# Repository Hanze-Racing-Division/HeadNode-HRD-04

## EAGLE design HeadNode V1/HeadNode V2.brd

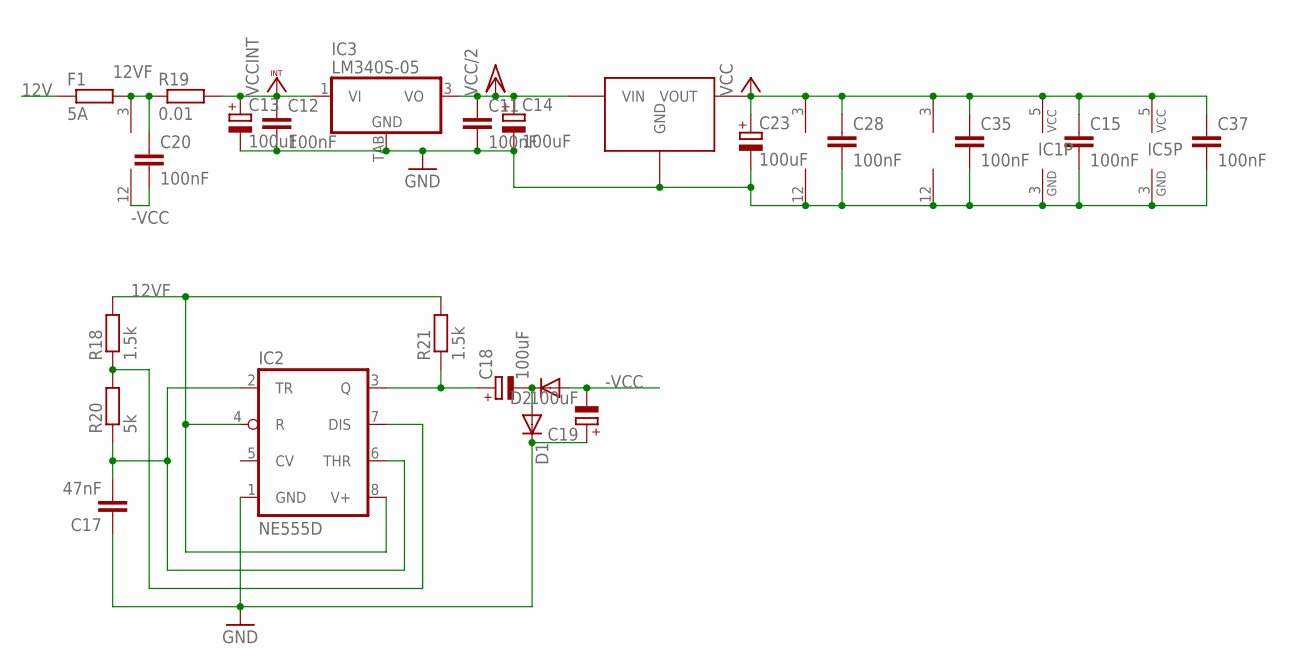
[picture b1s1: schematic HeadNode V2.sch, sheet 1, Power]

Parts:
C11, C12, C15, C20, C28, C35, C37: 100nF; C0805
C13, C14, C23: 100uF; 153CLV-0605; FARNELL 1244406RL
C17: 47nF; C0805; FARNELL MCSH31B473K160CT
C18, C19: 100uF; PANASONIC_D; FARNELL 1244406RL
D1, D2: DIODE-DO214AA; DO214AA; FARNELL SS13B
F1: 5A; R1206; FARNELL MC12CF 005
IC1, IC5: 74AHCT1G14DBV; SOT23-5
IC2: NE555D; SO08
IC3: LM340S-05; TO263-3; FARNELL LM1084ISX-5.0/NOPB
IC4, IC6, IC7: LM339D; SO14
R18, R21: 1.5k; R0805
R19: 0.01; R4527; FARNELL OARS1 - R010FI
R20: 5k; R0805
U$5: TS2940; TO-252

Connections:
12V: F1.1; also elsewhere on the board
12VF: C20.1, F1.2, IC2.4 (R), IC2.8 (V+), IC4.3 (V+), R18.2, R19.1, R21.2; also elsewhere on the board
-VCC: C19.-, C20.2, D2.A, IC4.12 (GND)
GND: C11.2, C12.2, C13.-, C14.-, C15.2, C17.1, C19.+, C23.-, C28.2, C35.2, C37.2, D1.C, IC1.3 (GND), IC2.1 (GND), IC3.TAB (GND), IC5.3 (GND), IC6.12 (GND), IC7.12 (GND), U$5.GND; also elsewhere on the board
unnamed: C18.+, IC2.3 (Q), R21.1
unnamed: C18.-, D1.A, D2.C
unnamed: IC2.7 (DIS), R18.1, R20.2
unnamed: C17.2, IC2.2 (TR), IC2.6 (THR), R20.1
VCC: C15.1, C23.+, C28.1, C35.1, C37.1, IC1.5 (VCC), IC5.5 (VCC), IC6.3 (V+), IC7.3 (V+), U$5.VOUT; also elsewhere on the board
VCC/2: C11.1, C14.+, IC3.3 (VO), U$5.VIN; also elsewhere on the board
VCCINT: C12.1, C13.+, IC3.1 (VI), R19.2; also elsewhere on the board

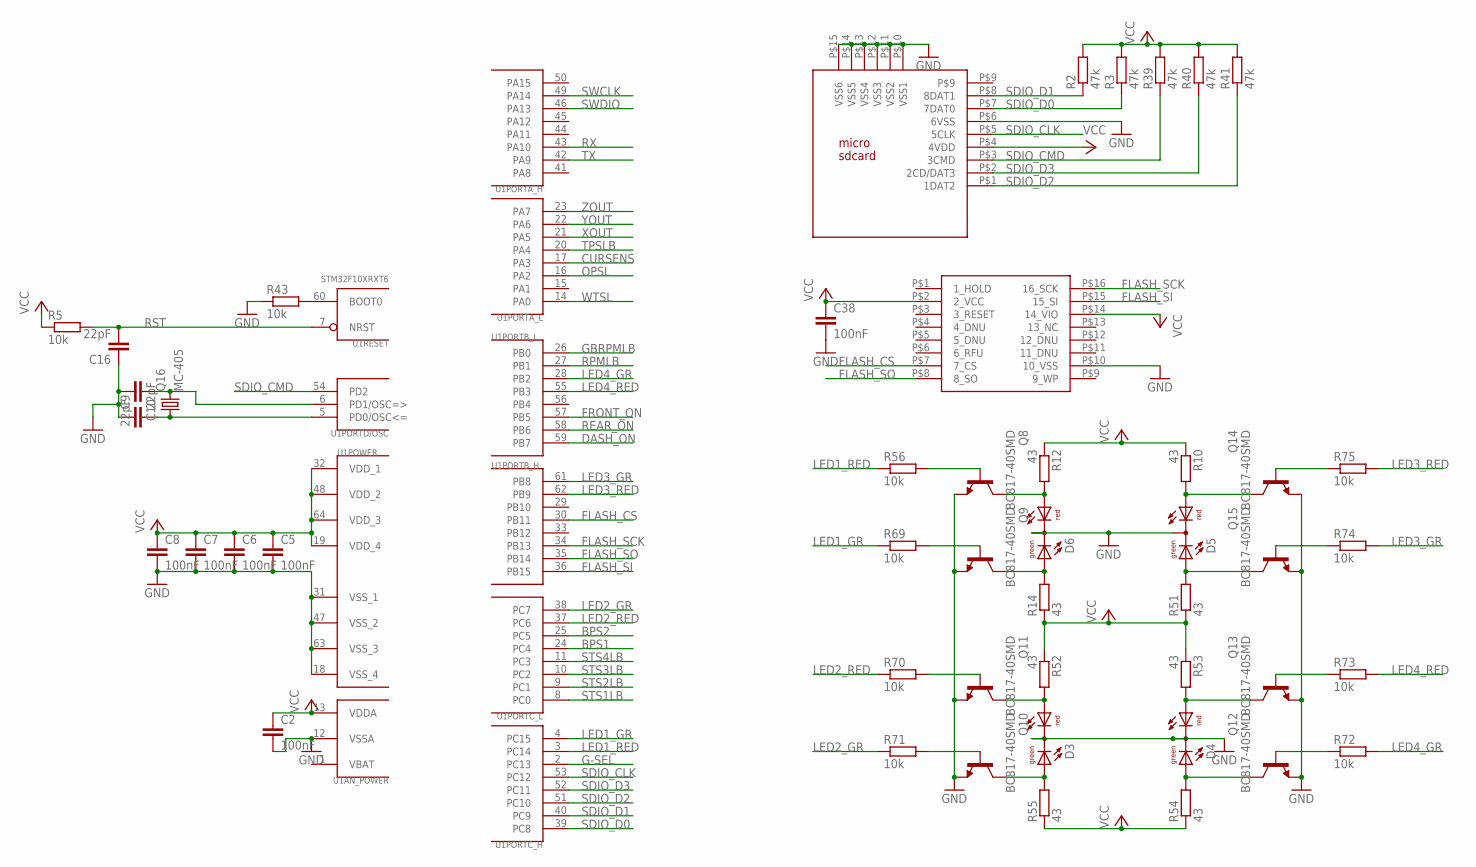
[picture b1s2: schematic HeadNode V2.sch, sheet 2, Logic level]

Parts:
C2, C5, C6, C7, C8, C38: 100nF; C0805
C9, C10, C16: 22pF; C0805
D3, D4, D5, D6: DUOLED5MM; FARNELL 8007627
Q8, Q9, Q10, Q11, Q12, Q13, Q14, Q15: BC817-40SMD; SOT23-BEC
Q16: MC-405
R2, R3, R39, R40, R41: 47k; R0805
R5, R43: 10k; M0805
R10, R12, R14, R51, R52, R53, R54, R55: 43; R0805
R56, R69, R70, R71, R72, R73, R74, R75: 10k; R0805
U1: STM32F10XRXT6; TQFP64
U$2: MICRO; FARNELL 2134442
U$7: S25FL512SAGMFIG11; 16SOIC; FARNELL 2340548

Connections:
BPS1: U1.24 (PC4); also elsewhere on the board
BPS2: U1.25 (PC5); also elsewhere on the board
CURSENS: U1.17 (PA3); also elsewhere on the board
DASH_ON: U1.59 (PB7); also elsewhere on the board
FLASH_CS: U1.30 (PB11), U$7.P$7 (7_CS)
FLASH_SCK: U1.34 (PB13), U$7.P$16 (16_SCK)
FLASH_SI: U1.36 (PB15), U$7.P$15 (15_SI)
FLASH_SO: U1.35 (PB14), U$7.P$8 (8_SO)
FRONT_ON: U1.57 (PB5); also elsewhere on the board
G-SEL: U1.2 (PC13); also elsewhere on the board
GBRPMLB: U1.26 (PB0); also elsewhere on the board
GND: C2.2, C5.2, C6.2, C7.2, C8.2, C9.1, C10.2, C16.1, C38.2, D3.K (C), D4.K (C), D5.K (C), D6.K (C), Q8.E, Q9.E, Q10.E, Q11.E, Q12.E, Q13.E, Q14.E, Q15.E, R43.1, U1.12 (VSSA), U1.18 (VSS_4), U1.31 (VSS_1), U1.47 (VSS_2), U1.63 (VSS_3), U$2.P$6 (6VSS), U$2.P$10 (VSS1), U$2.P$11 (VSS2), U$2.P$12 (VSS3), U$2.P$13 (VSS4), U$2.P$14 (VSS5), U$2.P$15 (VSS6), U$7.P$10 (10_VSS); also elsewhere on the board
LED1_GR: R69.1, U1.4 (PC15)
LED1_RED: R56.1, U1.3 (PC14)
LED2_GR: R71.1, U1.38 (PC7)
LED2_RED: R70.1, U1.37 (PC6)
LED3_GR: R74.2, U1.61 (PB8)
LED3_RED: R75.2, U1.62 (PB9)
LED4_GR: R72.2, U1.28 (PB2)
LED4_RED: R73.2, U1.55 (PB3)
unnamed: R43.2, U1.60 (BOOT0)
unnamed: C9.2, Q16.1, U1.5 (PD0/OSC<=)
unnamed: C10.1, Q16.2, U1.6 (PD1/OSC=>)
unnamed: D5.AR, Q14.C, R10.2
unnamed: D6.AR, Q8.C, R12.2
unnamed: D6.AG, Q9.C, R14.2
unnamed: D5.AG, Q15.C, R51.2
unnamed: D3.AR, Q11.C, R52.2
unnamed: D4.AR, Q13.C, R53.2
unnamed: D4.AG, Q12.C, R54.2
unnamed: D3.AG, Q10.C, R55.2
unnamed: Q8.B, R56.2
unnamed: Q9.B, R69.2
unnamed: Q11.B, R70.2
unnamed: Q10.B, R71.2
unnamed: Q12.B, R72.1
unnamed: Q13.B, R73.1
unnamed: Q15.B, R74.1
unnamed: Q14.B, R75.1
OPSL: U1.16 (PA2); also elsewhere on the board
REAR_ON: U1.58 (PB6); also elsewhere on the board
RPMLB: U1.27 (PB1); also elsewhere on the board
RST: C16.2, R5.2, U1.7 (NRST); also elsewhere on the board
RX: U1.43 (PA10); also elsewhere on the board
SDIO_CLK: U1.53 (PC12), U$2.P$5 (5CLK)
SDIO_CMD: R39.1, U1.54 (PD2), U$2.P$3 (3CMD)
SDIO_D0: R3.1, U1.39 (PC8), U$2.P$7 (7DAT0)
SDIO_D1: R2.1, U1.40 (PC9), U$2.P$8 (8DAT1)
SDIO_D2: R41.1, U1.51 (PC10), U$2.P$1 (1DAT2)
SDIO_D3: R40.1, U1.52 (PC11), U$2.P$2 (2CD/DAT3)
STS1LB: U1.8 (PC0); also elsewhere on the board
STS2LB: U1.9 (PC1); also elsewhere on the board
STS3LB: U1.10 (PC2); also elsewhere on the board
STS4LB: U1.11 (PC3); also elsewhere on the board
SWCLK: U1.49 (PA14); also elsewhere on the board
SWDIO: U1.46 (PA13); also elsewhere on the board
TPSLB: U1.20 (PA4); also elsewhere on the board
TX: U1.42 (PA9); also elsewhere on the board
VBAT: U1.1 (VBAT)
VCC: C2.1, C5.1, C6.1, C7.1, C8.1, C38.1, R2.2, R3.2, R5.1, R10.1, R12.1, R14.1, R39.2, R40.2, R41.2, R51.1, R52.1, R53.1, R54.1, R55.1, U1.13 (VDDA), U1.19 (VDD_4), U1.32 (VDD_1), U1.48 (VDD_2), U1.64 (VDD_3), U$2.P$4 (4VDD), U$7.P$2 (2_VCC), U$7.P$14 (14_VIO); also elsewhere on the board
WTSL: U1.14 (PA0); also elsewhere on the board
XOUT: U1.21 (PA5); also elsewhere on the board
YOUT: U1.22 (PA6); also elsewhere on the board
ZOUT: U1.23 (PA7); also elsewhere on the board

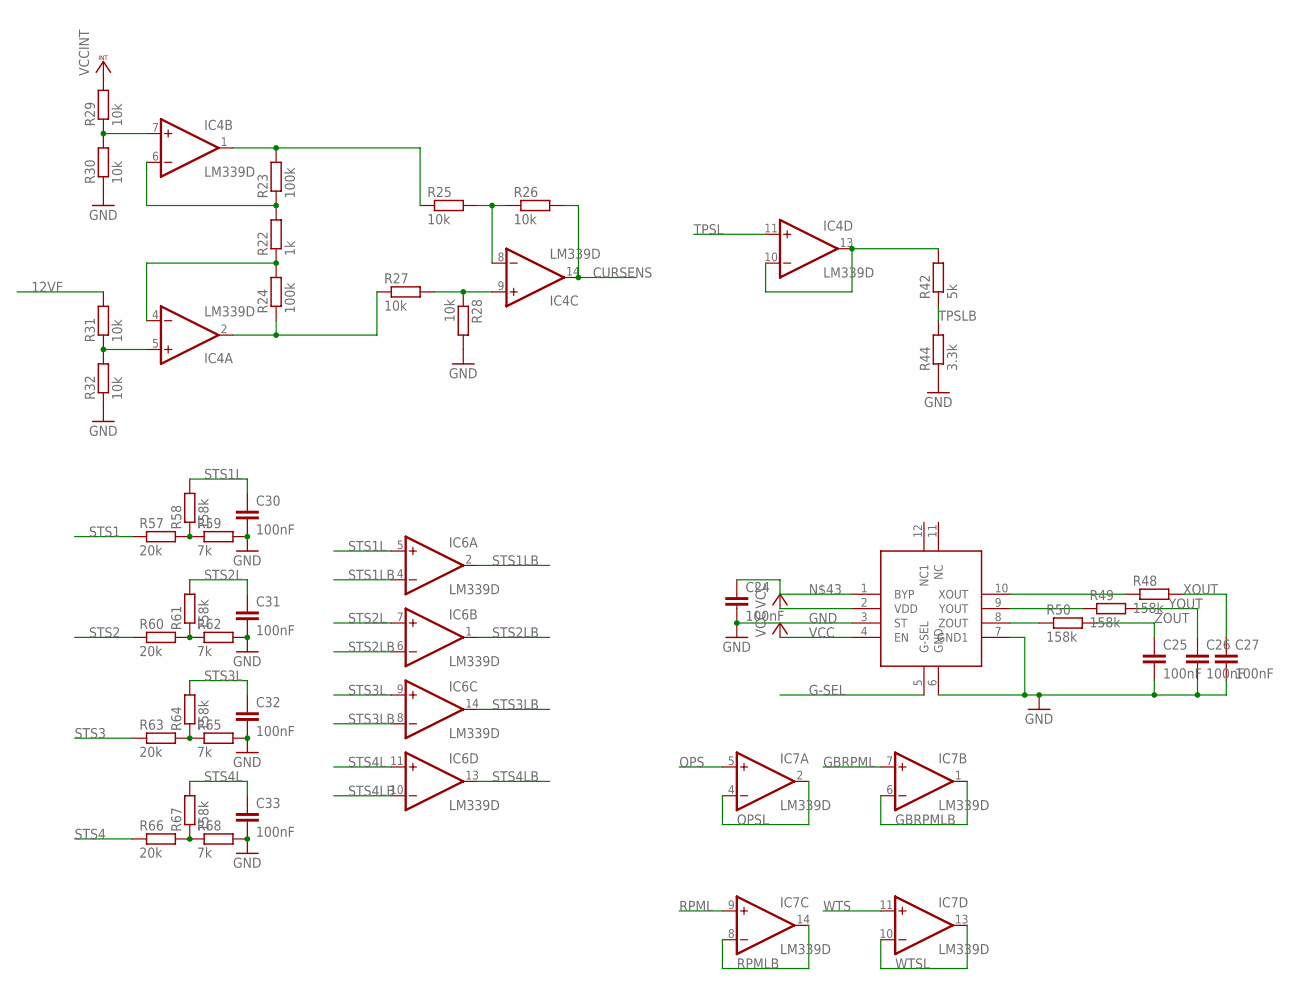
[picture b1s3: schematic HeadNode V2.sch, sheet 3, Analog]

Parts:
C24, C25, C26, C27, C30, C31, C32, C33: 100nF; C0805
IC4, IC6, IC7: LM339D; SO14
R22: 1k; M0805
R23, R24: 100k; M0805
R25, R26, R27, R28, R29, R30, R31, R32: 10k; M0805
R42: 5k; R0805
R44: 3.3k; R0805
R48, R49, R50, R58, R61, R64, R67: 158k; R0805
R57, R60, R63, R66: 20k; R0805
R59, R62, R65, R68: 7k; R0805
U$6: FXLN8371QR1; QFN; FARNELL 2450801

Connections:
12VF: R31.2; also elsewhere on the board
CURSENS: IC4.14 (OUT), R26.2; also elsewhere on the board
G-SEL: U$6.5 (G-SEL); also elsewhere on the board
GBRPML: IC7.7 (+IN); also elsewhere on the board
GBRPMLB: IC7.1 (OUT), IC7.6 (-IN); also elsewhere on the board
GND: C24.2, C25.2, C26.2, C27.2, C30.2, C31.2, C32.2, C33.2, R28.2, R30.1, R32.1, R44.1, R59.2, R62.2, R65.2, R68.2, U$6.3 (ST), U$6.6 (GND), U$6.7 (GND1); also elsewhere on the board
unnamed: IC4.6 (-IN), R22.2, R23.1
unnamed: IC4.4 (-IN), R22.1, R24.2
unnamed: IC4.9 (+IN), R27.2, R28.1
unnamed: IC4.1 (OUT), R23.2, R25.1
unnamed: IC4.8 (-IN), R25.2, R26.1
unnamed: IC4.7 (+IN), R29.1, R30.2
unnamed: IC4.5 (+IN), R31.1, R32.2
unnamed: R57.2, R58.1, R59.1
unnamed: IC4.10 (-IN), IC4.13 (OUT), R42.2
unnamed: IC4.2 (OUT), R24.1, R27.1
unnamed: R48.1, U$6.10 (XOUT)
unnamed: R49.1, U$6.9 (YOUT)
unnamed: R50.1, U$6.8 (ZOUT)
unnamed: C24.1, U$6.1 (BYP)
unnamed: R60.2, R61.1, R62.1
unnamed: R63.2, R64.1, R65.1
unnamed: R66.2, R67.1, R68.1
OPS: IC7.5 (+IN); also elsewhere on the board
OPSL: IC7.2 (OUT), IC7.4 (-IN); also elsewhere on the board
RPML: IC7.9 (+IN); also elsewhere on the board
RPMLB: IC7.8 (-IN), IC7.14 (OUT); also elsewhere on the board
STS1: R57.1; also elsewhere on the board
STS1L: C30.1, IC6.5 (+IN), R58.2
STS1LB: IC6.2 (OUT), IC6.4 (-IN); also elsewhere on the board
STS2: R60.1; also elsewhere on the board
STS2L: C31.1, IC6.7 (+IN), R61.2
STS2LB: IC6.1 (OUT), IC6.6 (-IN); also elsewhere on the board
STS3: R63.1; also elsewhere on the board
STS3L: C32.1, IC6.9 (+IN), R64.2
STS3LB: IC6.8 (-IN), IC6.14 (OUT); also elsewhere on the board
STS4: R66.1; also elsewhere on the board
STS4L: C33.1, IC6.11 (+IN), R67.2
STS4LB: IC6.10 (-IN), IC6.13 (OUT); also elsewhere on the board
TPSL: IC4.11 (+IN); also elsewhere on the board
TPSLB: R42.1, R44.2; also elsewhere on the board
VCC: U$6.2 (VDD), U$6.4 (EN); also elsewhere on the board
VCCINT: R29.2; also elsewhere on the board
WTS: IC7.11 (+IN); also elsewhere on the board
WTSL: IC7.10 (-IN), IC7.13 (OUT); also elsewhere on the board
XOUT: C27.1, R48.2; also elsewhere on the board
YOUT: C26.1, R49.2; also elsewhere on the board
ZOUT: C25.1, R50.2; also elsewhere on the board

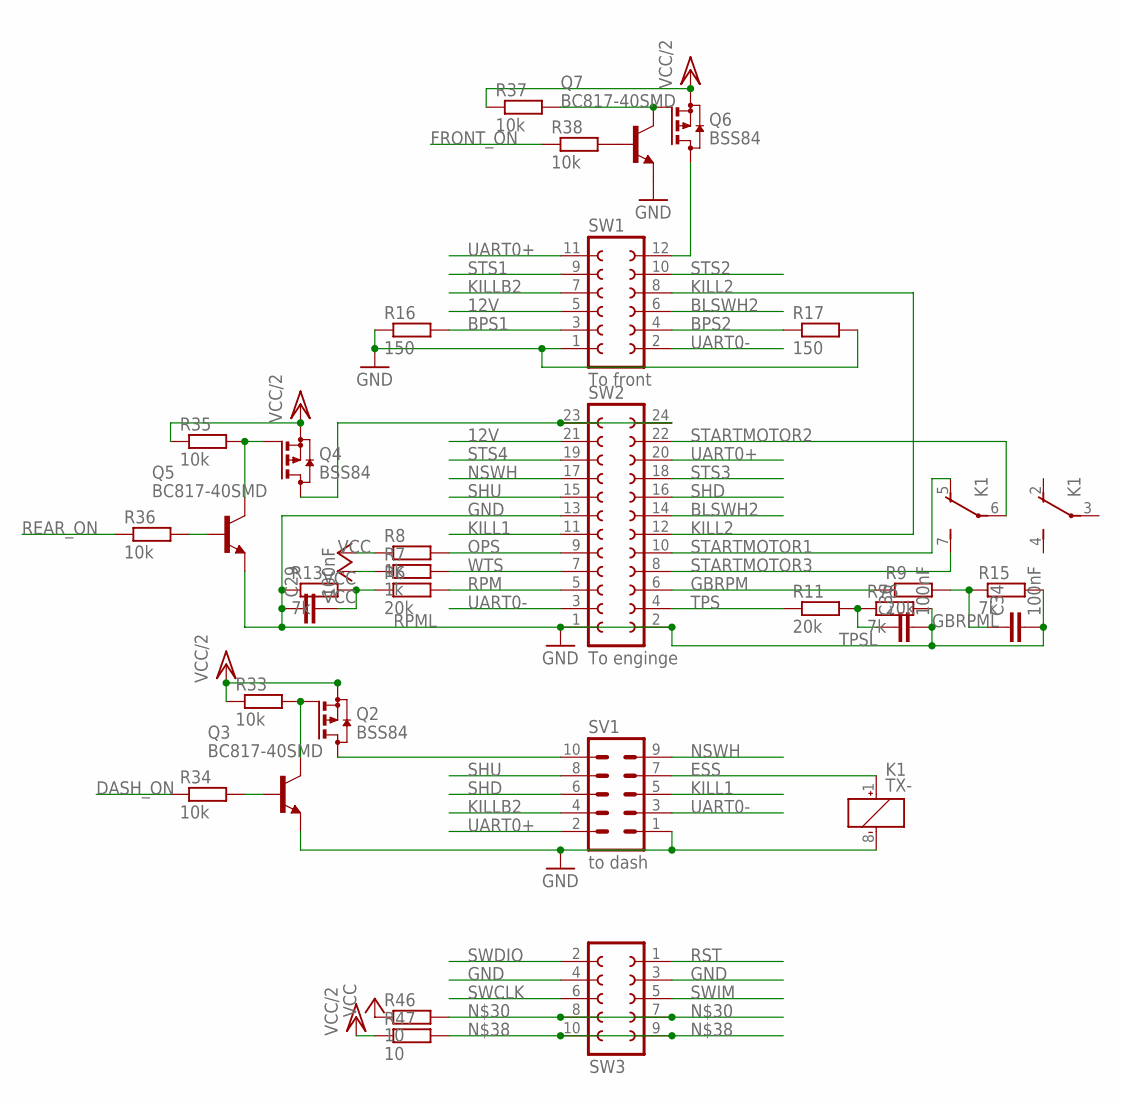
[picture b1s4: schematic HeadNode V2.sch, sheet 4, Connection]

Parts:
C29, C34, C36: 100nF; C0805
K1: TX-; AGQ; FARNELL AGQ210A4HZJ
Q2, Q4, Q6: BSS84; SOT23; FARNELL TSM2311CX
Q3, Q5, Q7: BC817-40SMD; SOT23-BEC
R6, R9, R11: 20k; R0805
R7, R8: 1k; R0805
R13, R15, R76: 7k; R0805
R16, R17: 150; R0805
R33, R34, R35, R36, R37, R38: 10k; R0805
R46, R47: 10; R0805
SV1: to dash; MA05-2
SW1: To front; FE06-2
SW2: To enginge; FE12-2
SW3: To front; FE05-2W

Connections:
12V: SW1.5, SW2.21; also elsewhere on the board
BLSWH2: SW1.6, SW2.14
BPS1: R16.2, SW1.3; also elsewhere on the board
BPS2: R17.1, SW1.4; also elsewhere on the board
DASH_ON: R34.1; also elsewhere on the board
ESS: K1.1 (+), SV1.7
FRONT_ON: R38.1; also elsewhere on the board
GBRPM: R9.1, SW2.6
GBRPML: C34.1, R9.2, R15.1; also elsewhere on the board
GND: C29.1, C34.2, C36.2, K1.8 (-), Q3.E, Q5.E, Q7.E, R13.1, R15.2, R16.1, R17.2, R76.2, SV1.1, SW1.1, SW2.1, SW2.2, SW2.13, SW3.3, SW3.4; also elsewhere on the board
KILL1: SV1.5, SW2.11
KILL2: SW1.8, SW2.12
KILLB2: SV1.4, SW1.7
unnamed: Q2.3 (D), SV1.10
unnamed: Q3.B, R34.2
unnamed: Q2.1 (G), Q3.C, R33.2
unnamed: Q4.3 (D), SW2.23, SW2.24
unnamed: Q4.1 (G), Q5.C, R35.2
unnamed: Q5.B, R36.2
unnamed: Q6.3 (D), SW1.12
unnamed: Q6.1 (G), Q7.C, R37.2
unnamed: Q7.B, R38.2
unnamed: R46.2, SW3.7, SW3.8
unnamed: R47.2, SW3.9, SW3.10
NSWH: SV1.9, SW2.17
OPS: R8.2, SW2.9; also elsewhere on the board
REAR_ON: R36.1; also elsewhere on the board
RPM: R6.2, SW2.5
RPML: C29.2, R6.1, R13.2; also elsewhere on the board
RST: SW3.1; also elsewhere on the board
SHD: SV1.6, SW2.16
SHU: SV1.8, SW2.15
STARTMOTOR1: K1.5 (O), SW2.10
STARTMOTOR2: K1.6, SW2.22
STARTMOTOR3: K1.7 (S), SW2.8
STS1: SW1.9; also elsewhere on the board
STS2: SW1.10; also elsewhere on the board
STS3: SW2.18; also elsewhere on the board
STS4: SW2.19; also elsewhere on the board
SWCLK: SW3.6; also elsewhere on the board
SWDIO: SW3.2; also elsewhere on the board
SWIM: SW3.5
TPS: R11.1, SW2.4
TPSL: C36.1, R11.2, R76.1; also elsewhere on the board
UART0+: SV1.2, SW1.11, SW2.20; also elsewhere on the board
UART0-: SV1.3, SW1.2, SW2.3; also elsewhere on the board
VCC: R7.1, R8.1, R46.1; also elsewhere on the board
VCC/2: Q2.2 (S), Q4.2 (S), Q6.2 (S), R33.1, R35.1, R37.1, R47.1; also elsewhere on the board
WTS: R7.2, SW2.7; also elsewhere on the board

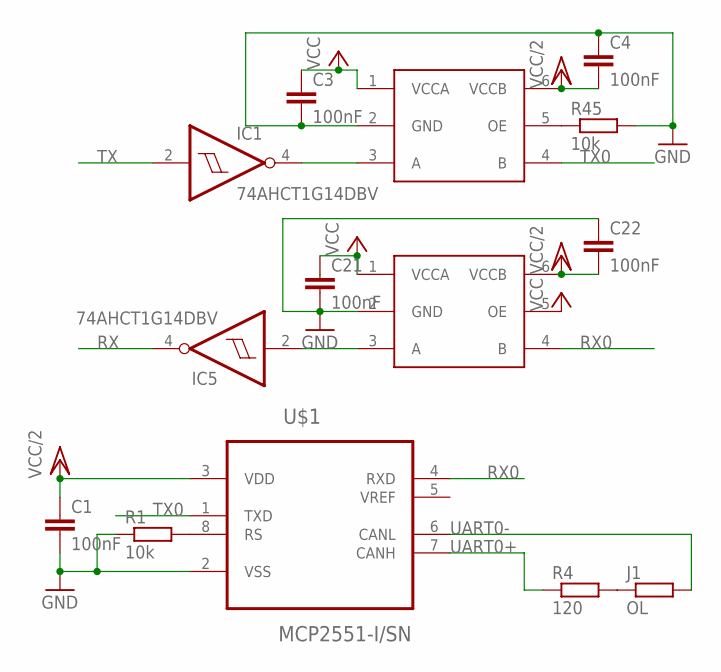
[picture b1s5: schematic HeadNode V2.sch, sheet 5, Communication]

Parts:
C1, C3, C4, C21, C22: 100nF; C0805
IC1, IC5: 74AHCT1G14DBV; SOT23-5
J1: OL; R0805
R1: 10k; M0805
R4: 120; R0805
R45: 10k; R0805
U$1: MCP2551-I/SN; SOIC127P600X175-8N
U$3, U$4: TXB0101; TSOT23-6_DDC

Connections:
GND: C1.2, C3.2, C4.1, C21.2, C22.1, R1.1, R45.2, U$1.2 (VSS), U$3.2 (GND), U$4.2 (GND); also elsewhere on the board
unnamed: R1.2, U$1.8 (RS)
unnamed: R45.1, U$3.5 (OE)
unnamed: IC1.4 (O), U$3.3 (A)
unnamed: IC5.2 (I), U$4.3 (A)
unnamed: J1.1, R4.2
RX: IC5.4 (O); also elsewhere on the board
RX0: U$1.4 (RXD), U$4.4 (B)
TX: IC1.2 (I); also elsewhere on the board
TX0: U$1.1 (TXD), U$3.4 (B)
UART0+: R4.1, U$1.7 (CANH); also elsewhere on the board
UART0-: J1.2, U$1.6 (CANL); also elsewhere on the board
VCC: C3.1, C21.1, U$3.1 (VCCA), U$4.1 (VCCA), U$4.5 (OE); also elsewhere on the board
VCC/2: C1.1, C4.2, C22.2, U$1.3 (VDD), U$3.6 (VCCB), U$4.6 (VCCB); also elsewhere on the board

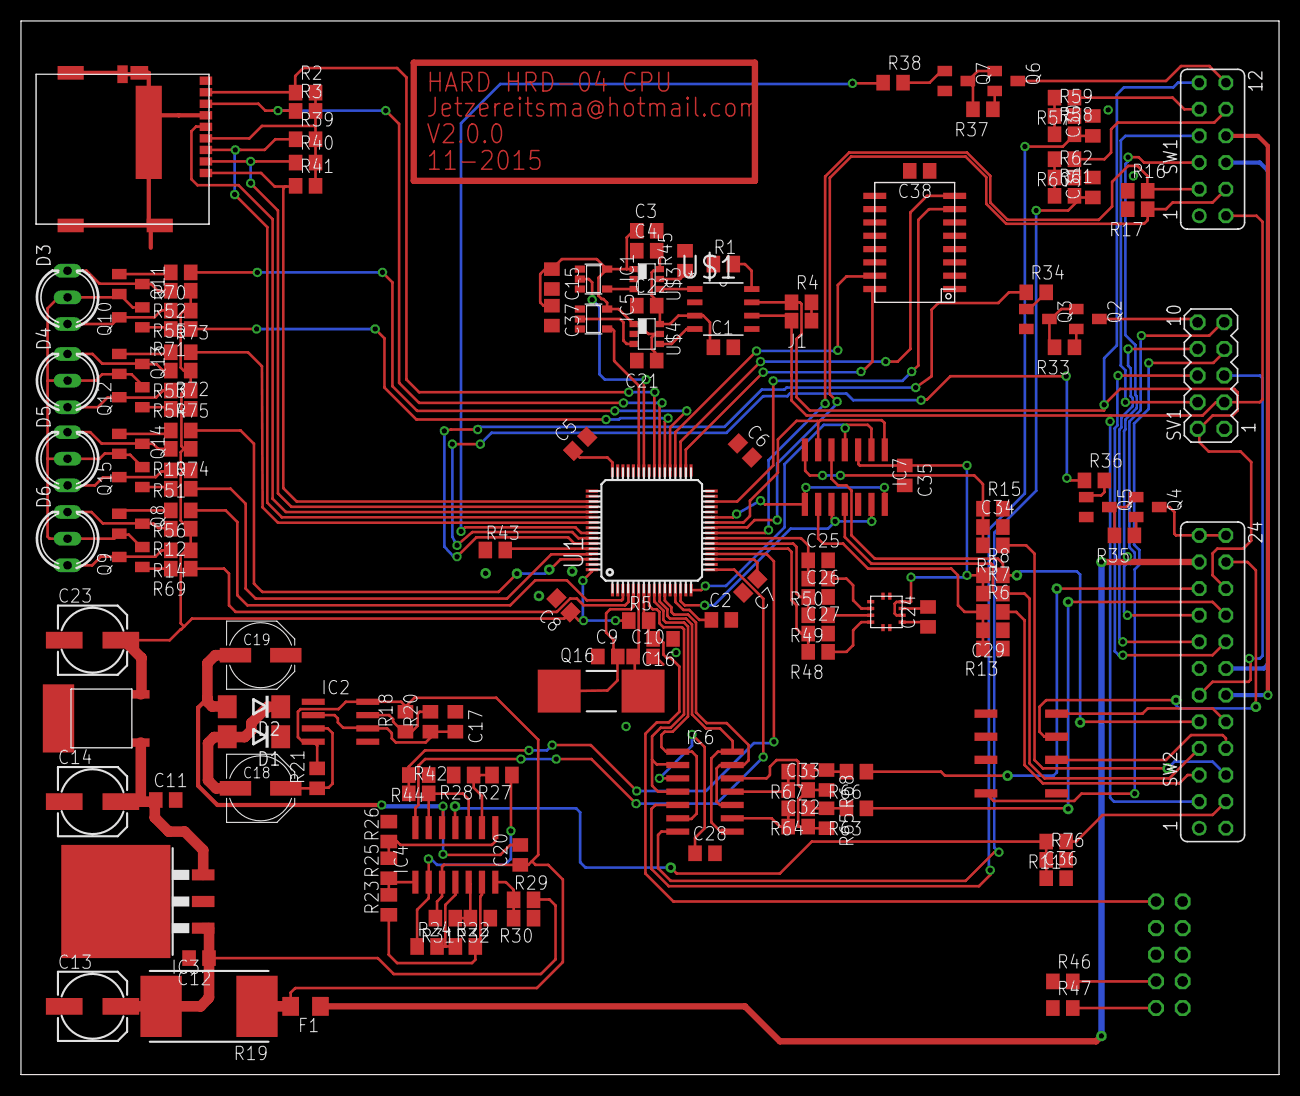
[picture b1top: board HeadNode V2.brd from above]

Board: 2 copper layers, 120.0 x 100.5 mm, 157 parts (1 on the bottom side), 136 nets.

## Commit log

2016-04-21 added eagle files
2016-04-21 added interrupttest project
